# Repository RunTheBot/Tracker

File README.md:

# Mesh Tracker
A Mesh Tracker based on Meshtastic, in the form of a compass!

## Features
- LCD For graphics
- Battery and Built-In Charger
- 9 Axis IMU (6 Axis + Magnometer)
- BLE, WiFi, LoRA
- Nearby Pairing

## How it works
Uses LoRa to transmit to the Meshtastic network on a private channel.

## Links
[CAD](https://cad.onshape.com/documents/e3691873ac5a479e26355872/w/654b772ea547b2e6e45daab3/e/722a3034d5cb82f9e90410ab)
[Firmware](https://github.com/runthebot/meshtastic)
[PCB](https://github.com/RunTheBot/Tracker/tree/main/PCB/tracker)
[BOM](https://docs.google.com/spreadsheets/d/1oAZxLPN-XNKiKrUyTvPvqBS-V4H7fdXqoOiTHCyojNU/edit?usp=sharing)

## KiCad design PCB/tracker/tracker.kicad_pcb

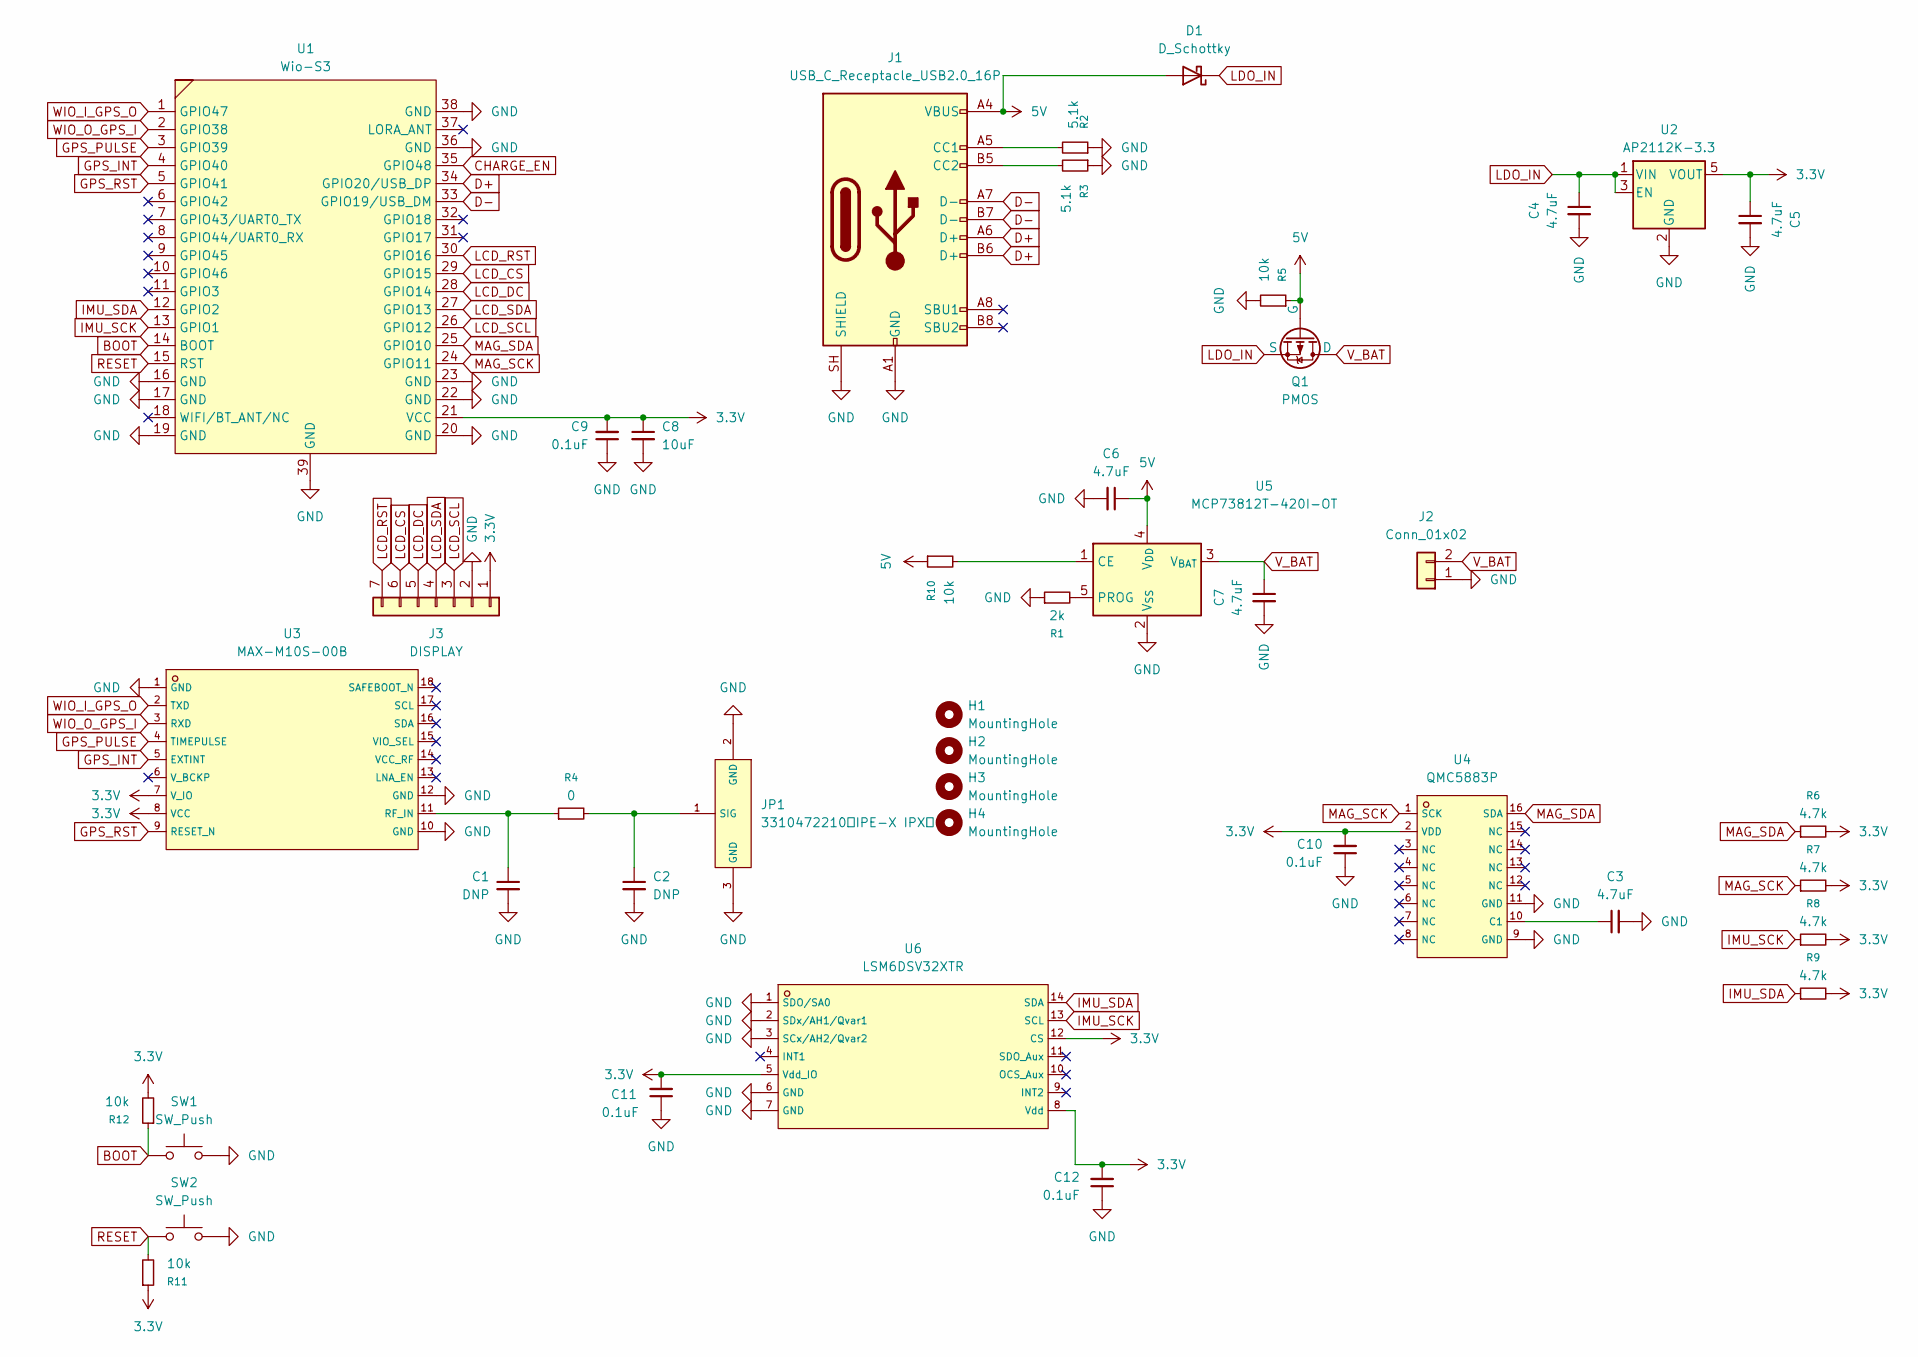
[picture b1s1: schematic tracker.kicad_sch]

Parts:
C1, C2: DNP; C_0402_1005Metric_Pad0.74x0.62mm_HandSolder
C3, C4, C5, C6, C7: 4.7uF; C_0603_1608Metric_Pad1.08x0.95mm_HandSolder
C8: 10uF; C_0603_1608Metric_Pad1.08x0.95mm_HandSolder
C9, C10, C11, C12: 0.1uF; C_0603_1608Metric_Pad1.08x0.95mm_HandSolder
D1: D_Schottky; D_SOD-123F
H1, H2, H3, H4: MountingHole; MountingHole_3.2mm_M3
J1: USB_C_Receptacle_USB2.0_16P; USB_C_Receptacle_G-Switch_GT-USB-7010ASV
J2: Conn_01x02; JST_PH_S2B-PH-K_1x02_P2.00mm_Horizontal
J3: DISPLAY; PinSocket_1x07_P2.54mm_Vertical
JP1: 3310472210，IPE-X IPX，; C88374_RF-SMD_FRF05002-JSS103M; LCSC C88374
Q1: PMOS; SOT-23-3
R1: 2k; R_0603_1608Metric_Pad0.98x0.95mm_HandSolder
R2, R3: 5.1k; R_0603_1608Metric_Pad0.98x0.95mm_HandSolder
R4: 0; R_0402_1005Metric_Pad0.72x0.64mm_HandSolder
R5, R10, R11, R12: 10k; R_0603_1608Metric_Pad0.98x0.95mm_HandSolder
R6, R7, R8, R9: 4.7k; R_0603_1608Metric_Pad0.98x0.95mm_HandSolder
SW1, SW2: SW_Push; SW_SPST_TS-1088-xR020
U1: Wio-S3; Wio-S3 Wireless Module Hand Solder
U2: AP2112K-3.3; SOT-23-5
U3: MAX-M10S-00B; C4153167_SMD-18_L10_1-W9_7-P1_10-TL_SKG09F; LCSC C4153167
U4: QMC5883P; C2847467_LGA-16_L3_0-W3_0-P0_50-BL_SQ; LCSC C2847467
U5: MCP73812T-420I-OT; SOT-23-5
U6: LSM6DSV32XTR; C22461202_LGA-14L_L3_0-W2_5-P0_50-TL; LCSC C22461202

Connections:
3.3V: C5.1, C8.1, C9.2, C10.2, C11.2, C12.2, J3.1, R6.2, R7.2, R8.2, R9.2, R11.1, R12.2, U1.21 (VCC), U2.5 (VOUT), U3.7 (V_IO), U3.8 (VCC), U4.2 (VDD), U6.5 (Vdd_IO), U6.8 (Vdd), U6.12 (CS)
5V: C6.1, D1.2 (A), J1.A4 (VBUS), J1.A9 (VBUS), J1.B4 (VBUS), J1.B9 (VBUS), Q1.2 (G), R5.1, R10.1, U5.4 (V_{DD})
BOOT: R12.1, SW1.1, U1.14 (BOOT)
CHARGE_EN: U1.35 (GPIO48)
D+: J1.A6 (D+), J1.B6 (D+), U1.34 (GPIO20/USB_DP)
D-: J1.A7 (D-), J1.B7 (D-), U1.33 (GPIO19/USB_DM)
GND: C1.2, C2.2, C3.2, C4.2, C5.2, C6.2, C7.2, C8.2, C9.1, C10.1, C11.1, C12.1, J1.A1 (GND), J1.A12 (GND), J1.B1 (GND), J1.B12 (GND), J1.SH (SHIELD), J2.1, J3.2, JP1.2 (GND), JP1.3 (GND), R1.1, R2.1, R3.1, R5.2, SW1.2, SW2.2, U1.16 (GND), U1.17 (GND), U1.19 (GND), U1.20 (GND), U1.22 (GND), U1.23 (GND), U1.36 (GND), U1.38 (GND), U1.39 (GND), U2.2 (GND), U3.1 (GND), U3.10 (GND), U3.12 (GND), U4.9 (GND), U4.11 (GND), U5.2 (V_{SS}), U6.1 (SDO/SA0), U6.2 (SDx/AH1/Qvar1), U6.3 (SCx/AH2/Qvar2), U6.6 (GND), U6.7 (GND)
GPS_INT: U1.4 (GPIO40), U3.5 (EXTINT)
GPS_PULSE: U1.3 (GPIO39), U3.4 (TIMEPULSE)
GPS_RST: U1.5 (GPIO41), U3.9 (RESET_N)
IMU_SCK: R8.1, U1.13 (GPIO1), U6.13 (SCL)
IMU_SDA: R9.1, U1.12 (GPIO2), U6.14 (SDA)
LCD_CS: J3.6, U1.29 (GPIO15)
LCD_DC: J3.5, U1.28 (GPIO14)
LCD_RST: J3.7, U1.30 (GPIO16)
LCD_SCL: J3.3, U1.26 (GPIO12)
LCD_SDA: J3.4, U1.27 (GPIO13)
LDO_IN: C4.1, D1.1 (K), Q1.3 (S), U2.1 (VIN), U2.3 (EN)
MAG_SCK: R7.1, U1.24 (GPIO11), U4.1 (SCK)
MAG_SDA: R6.1, U1.25 (GPIO10), U4.16 (SDA)
unnamed: J1.A5 (CC1), R2.2
unnamed: J1.B5 (CC2), R3.2
unnamed: C2.1, JP1.1 (SIG), R4.2
unnamed: C1.1, R4.1, U3.11 (RF_IN)
unnamed: C3.1, U4.10 (C1)
unnamed: R10.2, U5.1 (CE)
unnamed: R1.2, U5.5 (PROG)
RESET: R11.2, SW2.1, U1.15 (RST)
V_BAT: C7.1, J2.2, Q1.1 (D), U5.3 (V_{BAT})
WIO_I_GPS_O: U1.1 (GPIO47), U3.2 (TXD)
WIO_O_GPS_I: U1.2 (GPIO38), U3.3 (RXD)

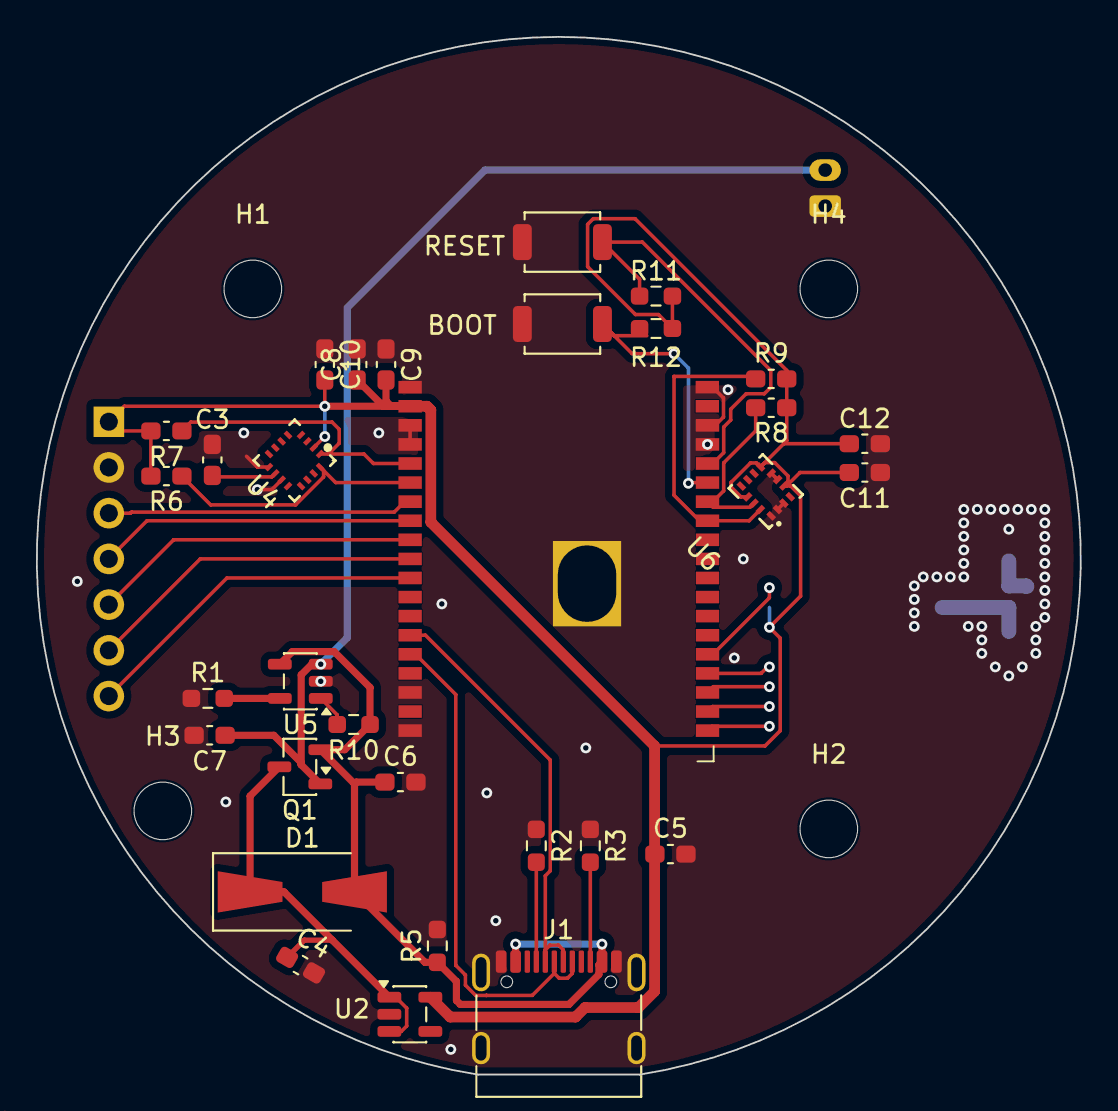
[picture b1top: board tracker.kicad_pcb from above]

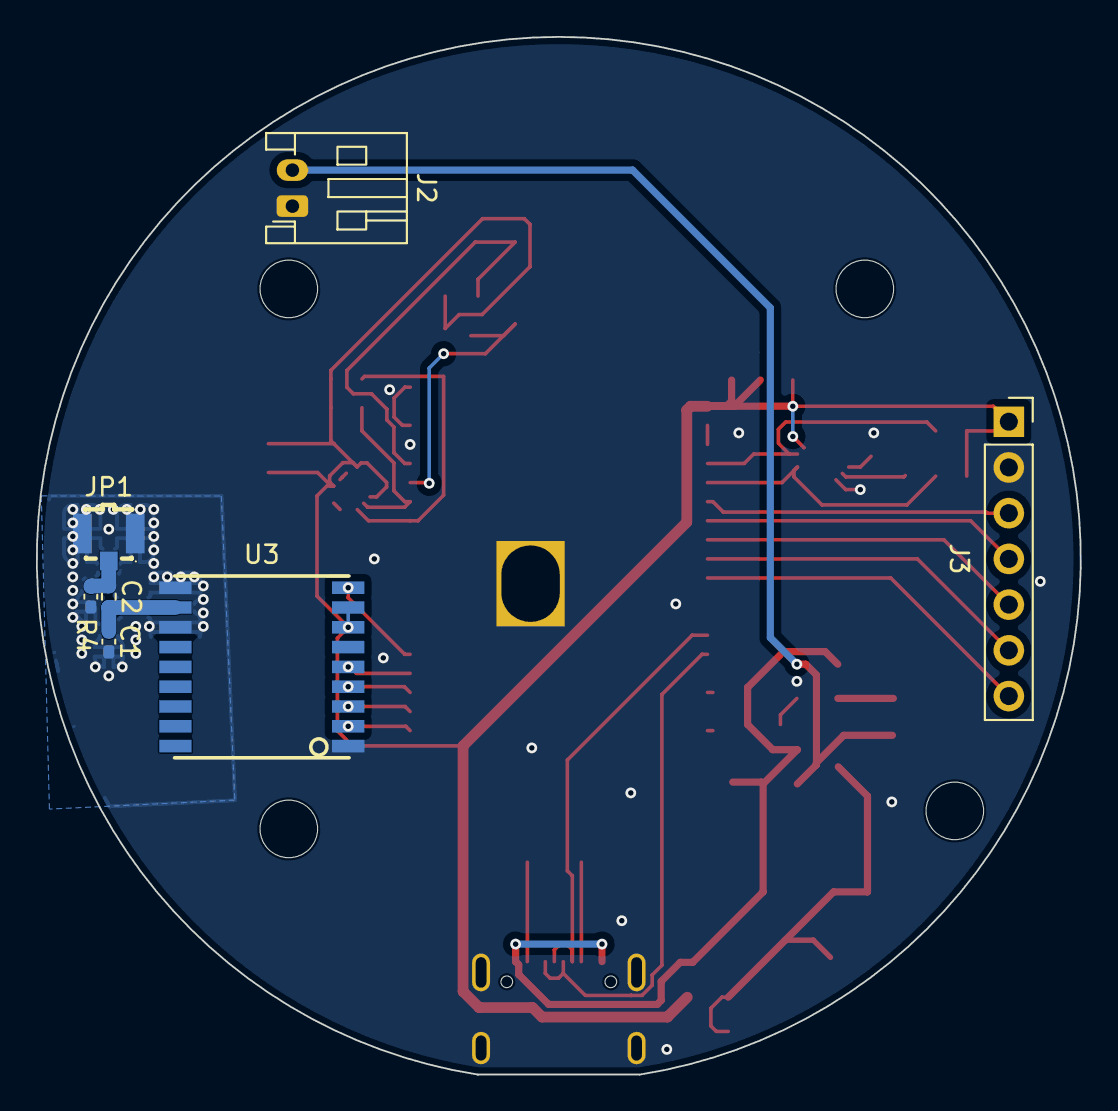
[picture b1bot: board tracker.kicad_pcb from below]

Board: 2 copper layers, 58.0 x 57.6 mm, 42 parts (7 on the bottom side), 30 nets.
